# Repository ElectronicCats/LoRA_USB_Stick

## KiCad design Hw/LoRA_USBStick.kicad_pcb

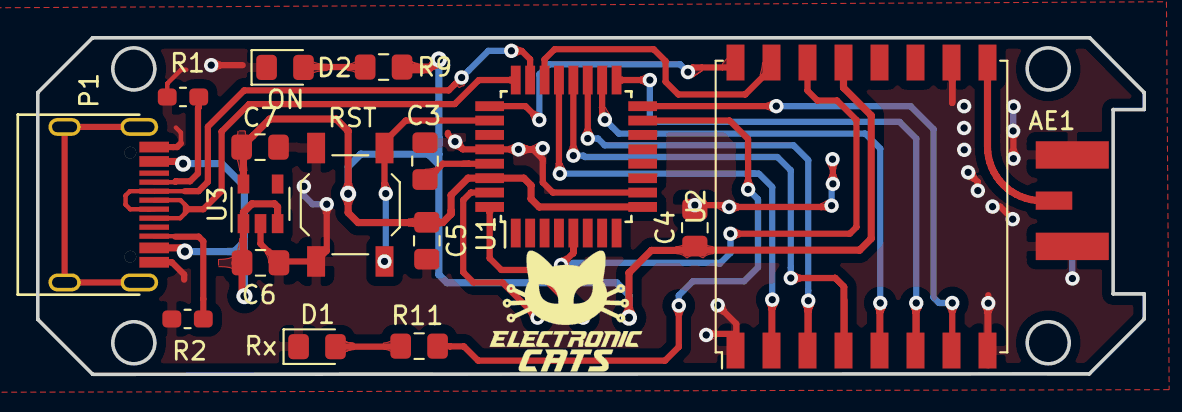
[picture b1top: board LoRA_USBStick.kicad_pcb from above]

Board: 2 copper layers, 61.5 x 18.7 mm, 18 parts (1 on the bottom side), 24 nets.

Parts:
AE1: Antenna_Shield; SMA_EDGE
C3: 1uF; C_0805_2012Metric_Pad1.15x1.40mm_HandSolder
C4, C5: 0.1uF; C_0805_2012Metric_Pad1.15x1.40mm_HandSolder
C6, C7: 10uF; C_0805_2012Metric_Pad1.15x1.40mm_HandSolder
D1: Rx; LED_0805_2012Metric_Pad1.15x1.40mm_HandSolder
D2: ON; LED_0805_2012Metric_Pad1.15x1.40mm_HandSolder
J4: SWD; Pin_Header_Straight_1x04_Pitch2.54mm
P1: USB_C_Plug_USB2.0; C393939
R1, R2: 5K1; R_0603_1608Metric_Pad1.05x0.95mm_HandSolder
R9, R11: 120R; R_0805_2012Metric_Pad1.15x1.40mm_HandSolder
SW1: RST; SW_SPST_TL3342
U1: ATSAMD21E; TQFP-32_7x7mm_Pitch0.8mm
U2: RFM95W-868S2; HOPERF_RFM9XW_SMD
U3: AP2112K-3.3; SOT-23-5

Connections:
+3V3: C4.1, C5.1, C7.1, J4.1, R9.1, U1.9, U1.30, U2.13, U3.5
/D+: P1.A6, U1.24
/D-: P1.A7, U1.23
/DIO0: U1.5, U2.14
/DIO1: U1.22, U2.15
/DIO2: U1.25, U2.16
/DIO5: U1.16, U2.7
/MISO: U1.21, U2.2
/MOSI: U1.19, U2.3
/RFM_RST: U1.17, U2.6
/RST: SW1.1, U1.26
/Rx_LED: R11.1, U1.15
/SCK: U1.20, U2.4
/SS: U1.18, U2.5
/SWCLK: J4.3, U1.31
/SWDIO: J4.2, U1.32
GND: AE1.2, C3.2, C4.2, C5.2, C6.2, C7.2, D1.1, D2.1, J4.4, P1.A1, R1.1, R2.1, SW1.2, U1.10, U1.28, U2.1, U2.8, U2.10, U3.2
unnamed: AE1.1, U2.9
unnamed: C3.1, U1.29
unnamed: D1.2, R11.2
unnamed: D2.2, R9.2
unnamed: P1.A5, R1.2
unnamed: P1.B5, R2.2
VBUS: C6.1, P1.A4, U3.1, U3.3

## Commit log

2020-09-05 add usb c and R
2020-09-08 Change_usb-C
2020-09-29 Change_in_connector
2020-09-29 Change in track
